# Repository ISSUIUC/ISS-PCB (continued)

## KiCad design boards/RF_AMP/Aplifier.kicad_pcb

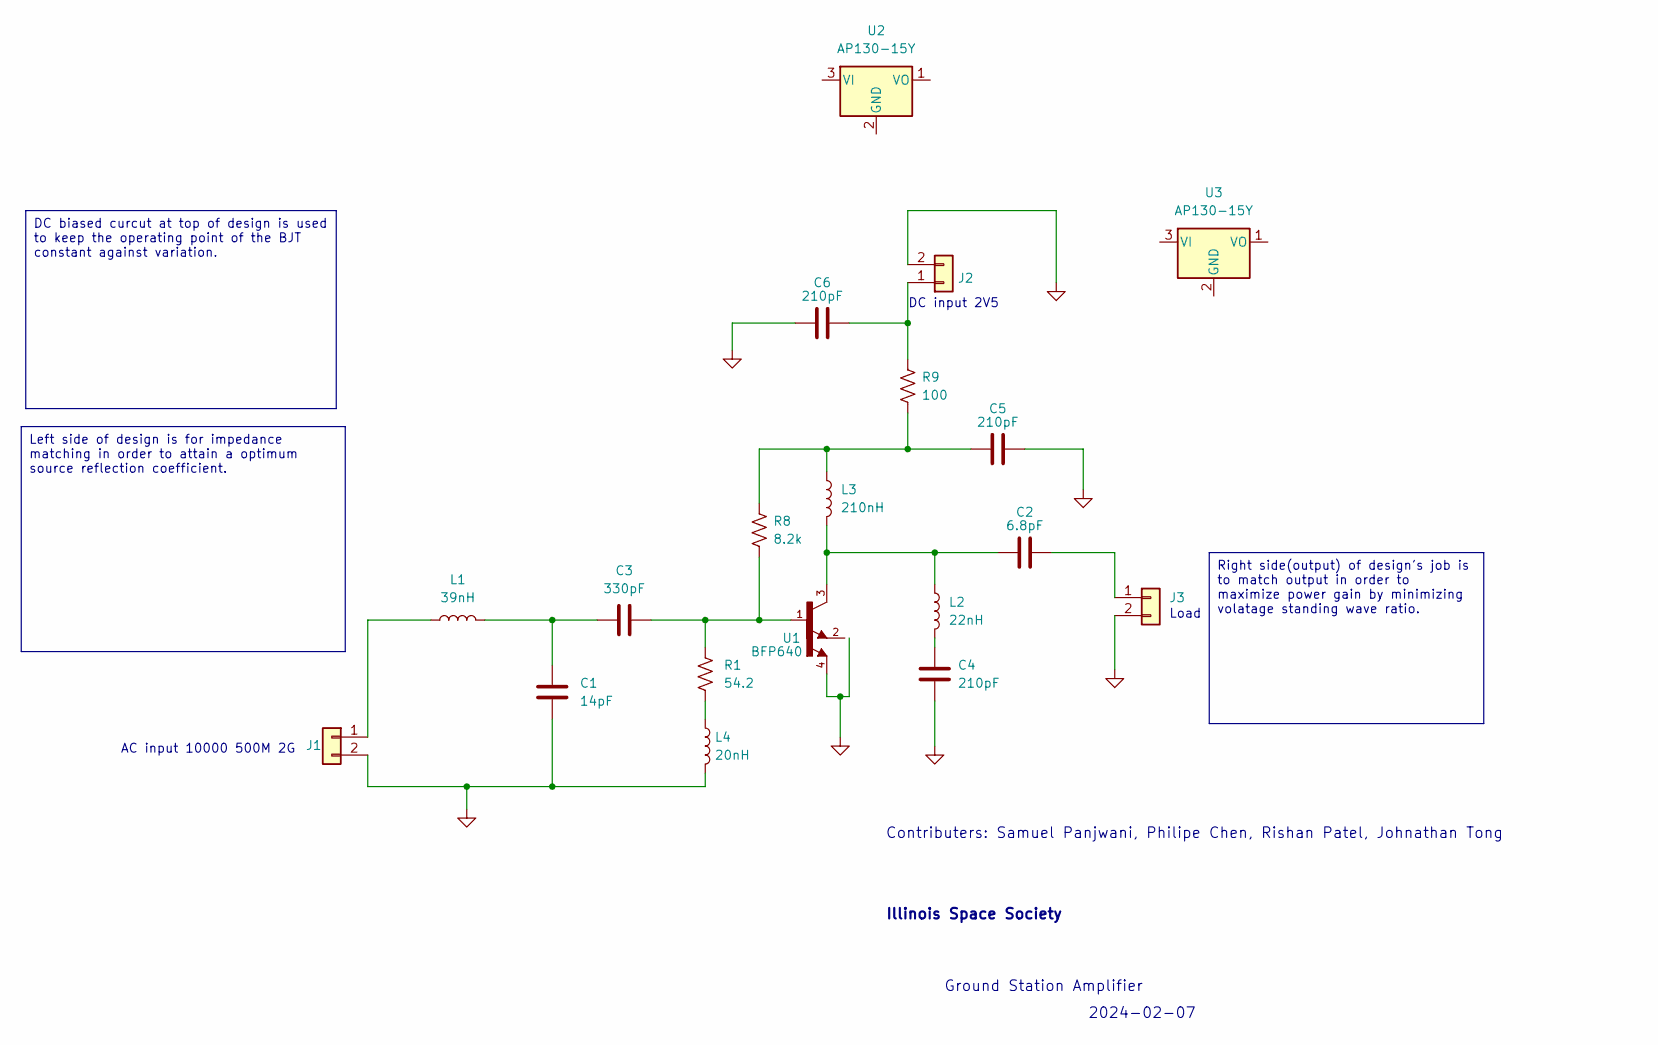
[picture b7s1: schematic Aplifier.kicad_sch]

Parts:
C1: 14pF; C_0201_0603Metric
C2: 6.8pF; C_0201_0603Metric
C3: 330pF; C_0201_0603Metric
C4, C5, C6: 210pF; C_0201_0603Metric
J1, J3: Conn_01x02; SMA_Molex_73251-1153_EdgeMount_Horizontal
J2: Conn_01x02; PinHeader_1x02_P1.27mm_Vertical
L1: 39nH; L_0201_0603Metric
L2: 22nH; L_0201_0603Metric
L3: 210nH; L_0201_0603Metric
L4: 20nH; L_0201_0603Metric
R1: 54.2; R_0201_0603Metric
R8: 8.2k; R_0201_0603Metric
R9: 100; R_0201_0603Metric
U1: BFP640; SOT343
U2, U3: AP130-15Y; SOT-89-3

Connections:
GND: C1.2, C4.2, C5.2, C6.2, J1.2, J2.2, J3.2, L4.2
unnamed: C1.1, C3.1, L1.2
unnamed: C2.2, L2.1, L3.2, U1.3
unnamed: C3.2, R1.1, R8.2, U1.1
unnamed: C4.1, L2.2
unnamed: C5.1, L3.1, R8.1, R9.2
unnamed: J1.1, L1.1
unnamed: C6.1, J2.1, R9.1
unnamed: C2.1, J3.1
unnamed: L4.1, R1.2

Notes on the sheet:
Right side(output) of design's job is to match output in order to maximize power gain by minimizing volatage standing wave ratio.
DC biased curcut at top of design is used to keep the operating point of the BJT constant against variation.
Left side of design is for impedance matching in order to attain a optimum source reflection coefficient.
Contributers: Samuel Panjwani, Philipe Chen, Rishan Patel, Johnathan Tong
Illinois Space Society
Load
AC input 10000 500M 2G
Ground Station Amplifier
2024-02-07
DC input 2V5

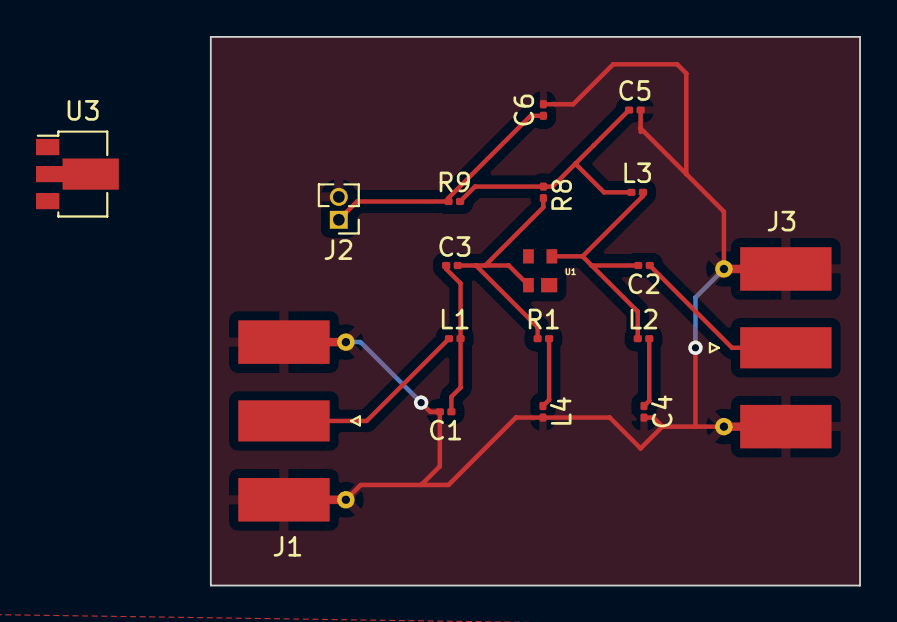
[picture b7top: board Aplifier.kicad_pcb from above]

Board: 2 copper layers, 36.1 x 30.5 mm, 18 parts (0 on the bottom side), 10 nets.
